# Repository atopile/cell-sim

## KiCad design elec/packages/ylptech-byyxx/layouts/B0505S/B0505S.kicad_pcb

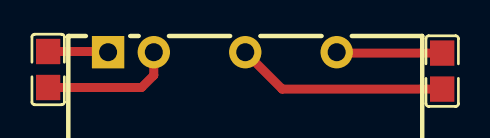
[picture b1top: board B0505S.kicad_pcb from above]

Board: 2 copper layers, 3 parts (0 on the bottom side), 4 nets.

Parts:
C1: 2.2µF; C0805
C2: 10µF; C0805
U1: PWRM-TH_BXXXXS-2WR3

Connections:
hv: C1.1, U1.1
lv: C1.2, U1.2
output_cap-power-hv: C2.1, U1.6
output_cap-power-lv: C2.2, U1.4

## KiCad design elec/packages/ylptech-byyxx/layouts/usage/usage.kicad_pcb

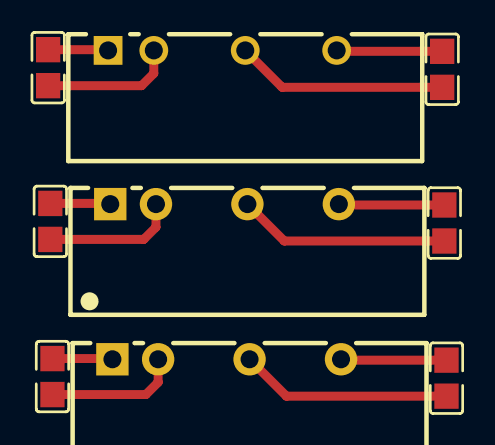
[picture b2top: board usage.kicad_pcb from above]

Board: 2 copper layers, 9 parts (0 on the bottom side), 12 nets.

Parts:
C1, C3, C5: 2.2µF; C0805
C2, C4, C6: 10µF; C0805
U1, U3: PWRM-TH_BXXXXS-2WR3
U2: PWRM-TH_BXXXXS-2WR2

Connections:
hv: C3.1, U2.1
lv: C3.2, U2.2
reg_5v_to_5v-power_in-hv: C1.1, U1.1
reg_5v_to_5v-power_in-lv: C1.2, U1.2
reg_5v_to_5v-power_out-hv: C2.1, U1.6
reg_5v_to_5v-power_out-lv: C2.2, U1.4
reg_12v_to_5v-power_out-hv: C4.1, U2.6
reg_12v_to_5v-power_out-lv: C4.2, U2.4
reg_24v_to_5v-power_in-hv: C5.1, U3.1
reg_24v_to_5v-power_in-lv: C5.2, U3.2
reg_24v_to_5v-power_out-hv: C6.1, U3.6
reg_24v_to_5v-power_out-lv: C6.2, U3.4
